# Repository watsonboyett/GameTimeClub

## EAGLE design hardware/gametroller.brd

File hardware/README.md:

## Revision History

### Rev. A

* Initial design

### Rev. B

* Added "power good" LED to 3V3 rail
* Removed silkscreen text for part numbers (just not enough room)
* Increased voltage output on 5V step-down converter 
* Added silkscreen text for pin numbers
* Fixed USB A pins (data lines were backwards)
* Added vias to micro USB shield pads to provide better mechanical support
* Added PTC fuse to micro USB port for over-current protection

### Future Changes

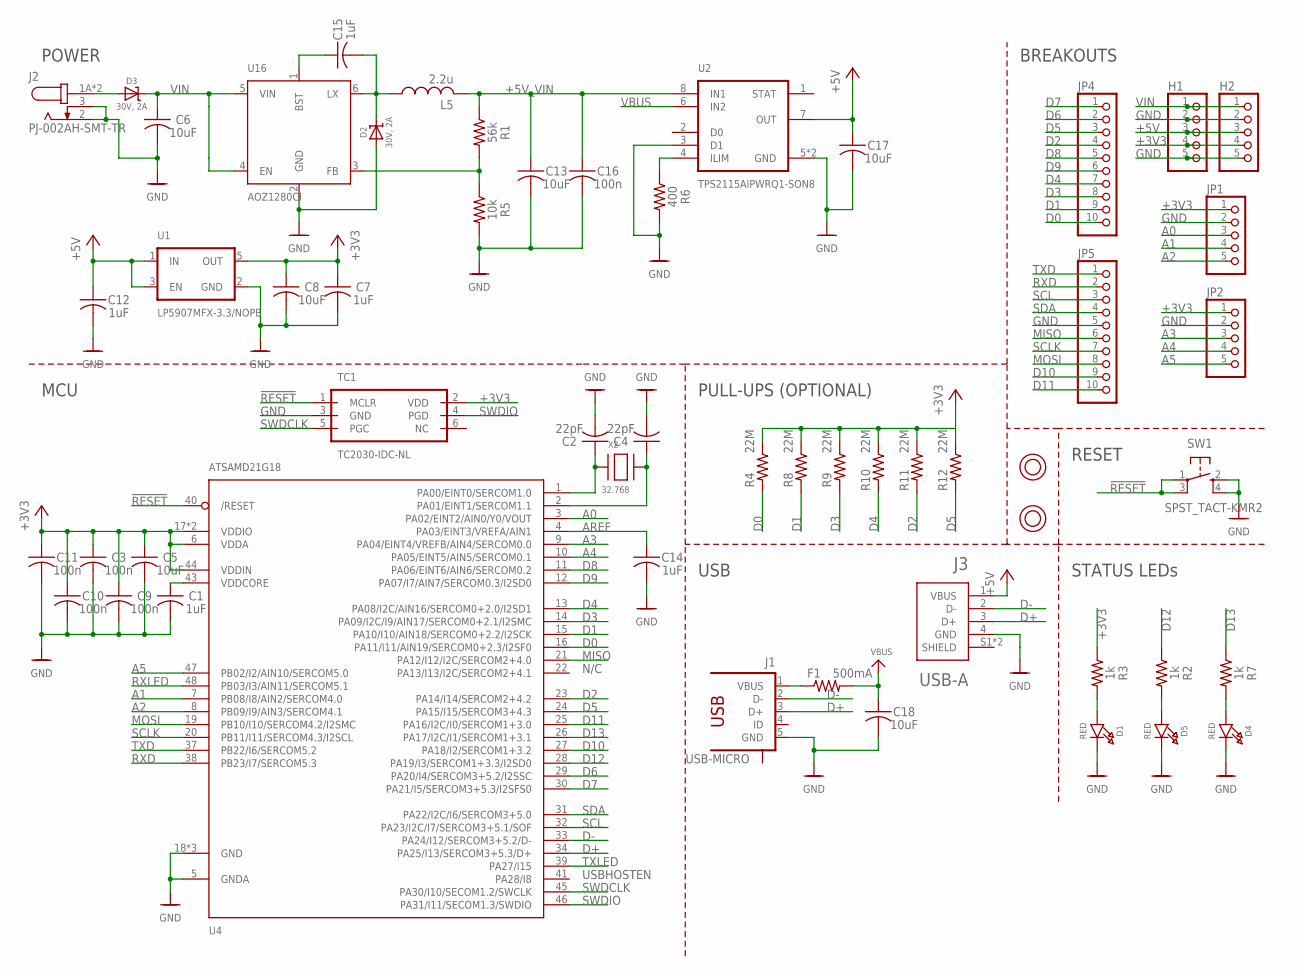
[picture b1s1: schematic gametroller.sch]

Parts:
C1, C7, C12, C14, C15: 1uF; C0603; MPN 0603ZC105KAT2A
C2, C4: 22pF; C0603; MPN C0603C220K4GACTU
C3, C9, C10, C11, C16: 100n; C0603; MPN C0603X104K5RAC7867
C5, C6, C8, C13, C17, C18: 10uF; C0805; MPN C2012JB1E106K085AC
D1, D4, D5: RED; CHIPLED_0805_NOOUTLINE; MPN LTST-C170GKT
D2, D3: 30V, 2A; SOD-128; MPN CMS06(TE12L,Q,M)
F1: 500mA; R0603; MPN MF-FSMF050X-2
H1, H2: PINHD-1X5-SMT; 1X05-SMT
J1: USB-MICRO; USB-10118192-0001LF
J2: PJ-002AH-SMT-TR; CUI_PJ-002AH-SMT-TR
J3: USB-A; CUI_UJ2-AH-1-SMT
JP1, JP2: PINHD-1X5-SMT; 1X05-SMT
JP4, JP5: PINHD-1X10-SMT; 1X10-SMT
L5: 2.2u; L5050M; MPN TYS50402R2N-10
R1: 56k; R0603; MPN ERJ-3EKF5602V
R2, R3, R7: 1k; R0603; MPN ERJ-3EKF1001V
R4, R8, R9, R10, R11, R12: 22M; R0603; MPN ERJ-3GEYK226V
R5: 10k; R0603; MPN ERJ-3GEYJ103V
R6: 400; R0603; MPN ERJ-3EKF4020V
SW1: SPST_TACT-KMR2; KMR2; MPN KMR211GLFS
TC1: TC2030-IDC-NL
U1: LP5907MFX-3.3/NOPB; SOT95P280X145-5N
U2: TPS2115AIPWRQ1-SON8; SON65P300X300X100-9N
U4: ATSAMD21G18; TQFP48_7MM
U16: AOZ1280CI; SOT-23-6
U$7, U$9: TERM-7774
X2: 32.768; XTAL3215; MPN ECS-.327-12.5-34B-TR

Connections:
!RESET: SW1.1, SW1.3 (P1), TC1.1 (MCLR), U4.40 (/RESET)
+3V3: C3.1, C5.1, C7.1, C8.1, C9.1, C10.1, C11.1, H1.4, H2.4, JP1.1, JP2.1, R3.1, R4.1, R8.1, R9.1, R10.1, R11.1, R12.1, TC1.2 (VDD), U1.5 (OUT), U4.6 (VDDA), U4.17 (VDDIO), U4.36 (VDDIO), U4.44 (VDDIN)
+5V: C12.1, C17.1, H1.3, H2.3, J3.1 (VBUS), U1.1 (IN), U1.3 (EN), U2.7 (OUT)
+5V_VIN: C13.1, C16.1, L5.2, R1.1, U2.8 (IN1)
A0: JP1.3, U4.3 (PA02/EINT2/AIN0/Y0/VOUT)
A1: JP1.4, U4.7 (PB08/I8/AIN2/SERCOM4.0)
A2: JP1.5, U4.8 (PB09/I9/AIN3/SERCOM4.1)
A3: JP2.3, U4.9 (PA04/EINT4/VREFB/AIN4/SERCOM0.0)
A4: JP2.4, U4.10 (PA05/EINT5/AIN5/SERCOM0.1)
A5: JP2.5, U4.47 (PB02/I2/AIN10/SERCOM5.0)
AREF: C14.1, U4.4 (PA03/EINT3/VREFA/AIN1)
D0: JP4.10, R4.2, U4.16 (PA11/I11/AIN19/SERCOM0+2.3/I2SF0)
D1: JP4.9, R8.2, U4.15 (PA10/I10/AIN18/SERCOM0+2.2/I2SCK)
D2: JP4.4, R11.2, U4.23 (PA14/I14/SERCOM2+4.2)
D3: JP4.8, R9.2, U4.14 (PA09/I2C/I9/AIN17/SERCOM0+2.1/I2SMC)
D4: JP4.7, R10.2, U4.13 (PA08/I2C/AIN16/SERCOM0+2.0/I2SD1)
D5: JP4.3, R12.2, U4.24 (PA15/I15/SERCOM3+4.3)
D6: JP4.2, U4.29 (PA20/I4/SERCOM3+5.2/I2SSC)
D7: JP4.1, U4.30 (PA21/I5/SERCOM3+5.3/I2SFS0)
D8: JP4.5, U4.11 (PA06/EINT6/AIN6/SERCOM0.2)
D9: JP4.6, U4.12 (PA07/I7/AIN7/SERCOM0.3/I2SD0)
D10: JP5.9, U4.27 (PA18/I2/SERCOM1+3.2)
D11: JP5.10, U4.25 (PA16/I2C/I0/SERCOM1+3.0)
D12: R2.1, U4.28 (PA19/I3/SERCOM1+3.3/I2SD0)
D13: R7.1, U4.26 (PA17/I2C/I1/SERCOM1+3.1)
D+: J1.3 (D+), J3.3 (D+), U4.34 (PA25/I13/SERCOM3+5.3/D+)
D-: J1.2 (D-), J3.2 (D-), U4.33 (PA24/I12/SERCOM3+5.2/D-)
GND: C1.2, C2.2, C3.2, C4.2, C5.2, C6.2, C7.2, C8.2, C9.2, C10.2, C11.2, C12.2, C13.2, C14.2, C16.2, C17.2, C18.2, D1.C, D2.A, D4.C, D5.C, H1.2, H1.5, H2.2, H2.5, J1.5 (GND), J2.2, J2.3, J3.4 (GND), JP1.2, JP2.2, JP5.5, R5.2, R6.2, SW1.2 (S), SW1.4 (S1), TC1.3 (GND), U1.2 (GND), U2.3 (D1), U2.5 (GND), U2.9 (GND), U4.5 (GNDA), U4.18 (GND), U4.35 (GND), U4.42 (GND), U16.2 (GND)
LX: C15.2, D2.C, L5.1, U16.6 (LX)
MISO: JP5.6, U4.21 (PA12/I12/I2C/SERCOM2+4.0)
MOSI: JP5.8, U4.19 (PB10/I10/SERCOM4.2/I2SMC)
unnamed: D5.A, R2.2
unnamed: D4.A, R7.2
unnamed: D1.A, R3.2
unnamed: F1.1, J1.1 (VBUS)
unnamed: C2.1, U4.1 (PA00/EINT0/SERCOM1.0), X2.P$1
unnamed: C4.1, U4.2 (PA01/EINT1/SERCOM1.1), X2.P$2
unnamed: C15.1, U16.1 (BST)
unnamed: R6.1, U2.4 (ILIM)
unnamed: R1.2, R5.1, U16.3 (FB)
RXD: JP5.2, U4.38 (PB23/I7/SERCOM5.3)
RXLED: U4.48 (PB03/I3/AIN11/SERCOM5.1)
SCL: JP5.3, U4.32 (PA23/I2C/I7/SERCOM3+5.1/SOF)
SCLK: JP5.7, U4.20 (PB11/I11/SERCOM4.3/I2SCL)
SDA: JP5.4, U4.31 (PA22/I2C/I6/SERCOM3+5.0)
SWDCLK: TC1.5 (PGC), U4.45 (PA30/I10/SECOM1.2/SWCLK)
SWDIO: TC1.4 (PGD), U4.46 (PA31/I11/SECOM1.3/SWDIO)
TXD: JP5.1, U4.37 (PB22/I6/SERCOM5.2)
TXLED: U4.39 (PA27/I15)
VBUS: C18.1, F1.2, U2.6 (IN2)
VDDCORE: C1.1, U4.43 (VDDCORE)
VIN: C6.1, D3.C, H1.1, H2.1, U16.4 (EN), U16.5 (VIN)
VIN_PRE: D3.A, J2.1A (1), J2.1B (1)

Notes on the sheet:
POWER
RESET
N/C
USBHOSTEN
BREAKOUTS
STATUS LEDs
MCU
USB
PULL-UPS (OPTIONAL)

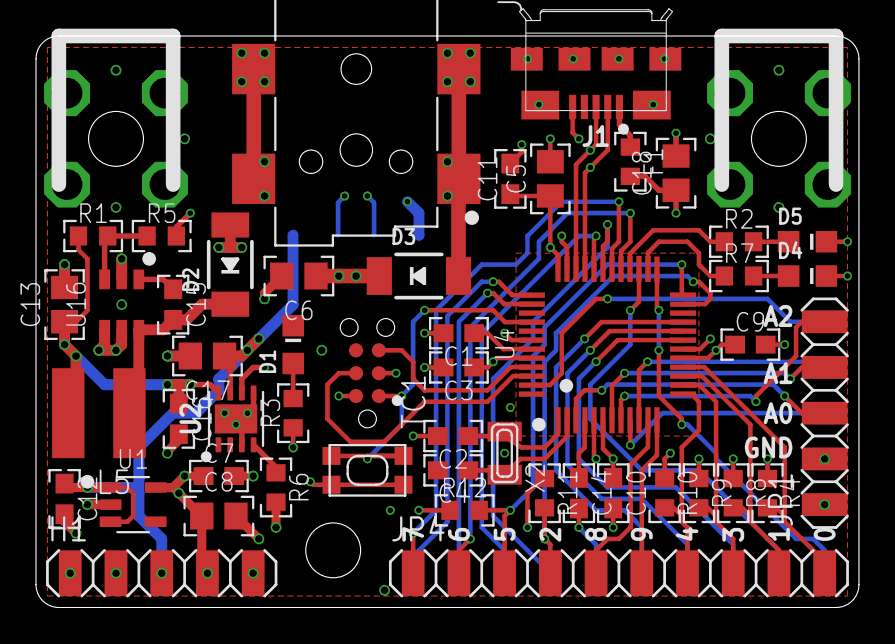
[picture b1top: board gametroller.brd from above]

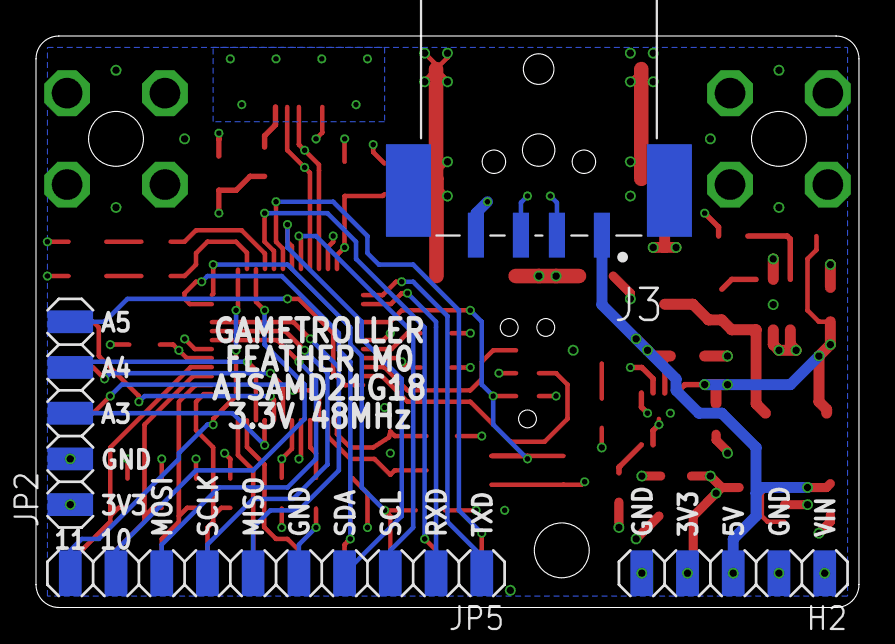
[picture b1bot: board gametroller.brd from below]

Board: 4 copper layers, 45.7 x 31.8 mm, 58 parts (4 on the bottom side), 51 nets.

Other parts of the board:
U$12, U$13, U$15: HOLE_4-40

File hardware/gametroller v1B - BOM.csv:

"Qty";"Value";"Device";"Package";"Parts";"Description";"MFG";"MPN";"PN-DK";
"2";"";"PINHD-1X10-SMT";"1X10-SMT";"JP4, JP5";"PIN HEADER";"";"";"";
"4";"";"PINHD-1X5-SMT";"1X05-SMT";"H1, H2, JP1, JP2";"PIN HEADER";"";"";"";
"5";"100n";"C-USC0603";"C0603";"C3, C9, C10, C11, C16";"CAPACITOR, American symbol";"KEMET";"C0603X104K5RAC7867";"399-7969-1-ND";
"1";"10k";"R-US_R0603";"R0603";"R5";"RESISTOR, American symbol";"Panasonic Electronic Components";"ERJ-3GEYJ103V";"P10KGCT-ND";
"6";"10uF";"C-USC0805";"C0805";"C5, C6, C8, C13, C17, C18";"CAPACITOR, American symbol";"TDK Corporation";"C2012JB1E106K085AC";"445-11462-1-ND";
"3";"1k";"R-US_R0603";"R0603";"R2, R3, R7";"RESISTOR, American symbol";"Panasonic Electronic Components";"ERJ-3EKF1001V";"P1.00KHCT-ND";
"5";"1uF";"C-USC0603";"C0603";"C1, C7, C12, C14, C15";"CAPACITOR, American symbol";"AVX Corporation";"0603ZC105KAT2A";"478-7940-1-ND";
"1";"2.2u";"L-USL5050M";"L5050M";"L5";"INDUCTOR, American symbol";"Laird-Signal Integrity Products";"TYS50402R2N-10";"240-2714-1-ND";
"6";"22M";"R-US_R0603";"R0603";"R4, R8, R9, R10, R11, R12";"RESISTOR, American symbol";"Panasonic Electronic Components";"ERJ-3GEYK226V";"P22MGCT-ND";
"2";"22pF";"C-USC0603";"C0603";"C2, C4";"CAPACITOR, American symbol";"KEMET";"C0603C220K4GACTU";"399-9031-1-ND";
"2";"30V, 2A";"DIODE-SCHOTTKYSOD-128";"SOD-128";"D2, D3";"";"Toshiba Semiconductor and Storage";"CMS06(TE12L,Q,M)";"CMS06QMCT-ND";
"1";"32.768";"XTAL-3.2X1.5";"XTAL3215";"X2";"Low cost SMT crystals, no capacitors included";"ECS Inc.";"ECS-.327-12.5-34B-TR";"XC1617CT-ND";
"1";"400";"R-US_R0603";"R0603";"R6";"RESISTOR, American symbol";"Panasonic Electronic Components";"ERJ-2RKF4020X";"P402LCT-ND";
"1";"500mA";"R-US_R0603";"R0603";"F1";"RESISTOR, American symbol";"Bel Fuse Inc.";"0ZCK0050FF2E";"507-1813-1-ND";
"1";"56k";"R-US_R0603";"R0603";"R1";"RESISTOR, American symbol";"Panasonic Electronic Components";"ERJ-3EKF5602V";"P56.0KHCT-ND";
"1";"AOZ1280CI";"AOZ1280CI";"SOT-23-6";"U16";"IC REG BUCK ADJ 1.2A SOT23-6";"Alpha & Omega Semiconductor Inc.";"AOZ1280CI";"785-1277-1-ND";
"1";"ATSAMD21G18";"ATSAMD21J_QFP";"TQFP48_7MM";"U4";"ARM® Cortex®-M0+ SAM D21G Microcontroller IC 32-Bit 48MHz 256KB (256K x 8) FLASH";"Microchip Technology";"ATSAMD21G18A";"ATSAMD21G18A-AU-ND";
"1";"LP5907MFX-3.3/NOPB";"LP5907MFX-3.3/NOPB";"SOT95P280X145-5N";"U1";"IC REG LINEAR 3.3V 250MA SOT23";"Texas Instruments";"LP5907MFX-3.3/NOPB";"296-38557-1-ND";
"1";"PJ-002AH-SMT-TR";"PJ-002AH-SMT-TR";"CUI_PJ-002AH-SMT-TR";"J2";"Power Barrel Connector Jack 2.00mm ID (0.079"), 5.50mm OD (0.217")";"CUI";"PJ-002AH-SMT-TR";"CP-002AHPJCT-ND";
"3";"RED";"LED0805_NOOUTLINE";"CHIPLED_0805_NOOUTLINE";"D1, D4, D5";"LED";"Lite-On Inc.";"LTST-C170GKT";"160-1179-1-ND";
"1";"SPST_TACT-KMR2";"SPST_TACT-KMR2";"KMR2";"SW1";"SMT 6mm switch, EVQQ2 series";"C&K";"KMR211GLFS";"401-1426-1-ND";
"1";"TC2030-IDC-NL";"TC2030-IDC-NL";"TC2030-IDC-NL";"TC1";"Tag-Connect In Circuit Programming & Debug Cable 6 Pin";"Tag-Connect";"TC2030-IDC";"";
"2";"TERM-7774";"TERM-7774";"TERM-7774";"U$7, U$9";"TERM SCREW 4-40 4 PIN PCB RA";"Keystone Electronics";"7774";"36-7774-ND";
"1";"TPS2115AIPWRQ1-SON8";"TPS2115AIPWRQ1-SON8";"SON65P300X300X100-9N";"U2";"AUTO-SWITCHING POWER MULTIPLEXER";"Texas Instruments";"TPS2115ADRBR";"296-23394-1-ND";
"1";"USB-A";"USB-A";"CUI_UJ2-AH-1-SMT";"J3";"USB - A USB 2.0 Receptacle Connector";"CUI";"UJ2-AH-1-SMT-TR";"102-4133-1-ND";
"1";"USB-MICRO";"USB-MICRO";"USB-10118192-0001LF";"J1";"CONN USB MICRO B RECPT SMT R/A";"Amphenol";"10118192-0001LF";"609-4613-1-ND";

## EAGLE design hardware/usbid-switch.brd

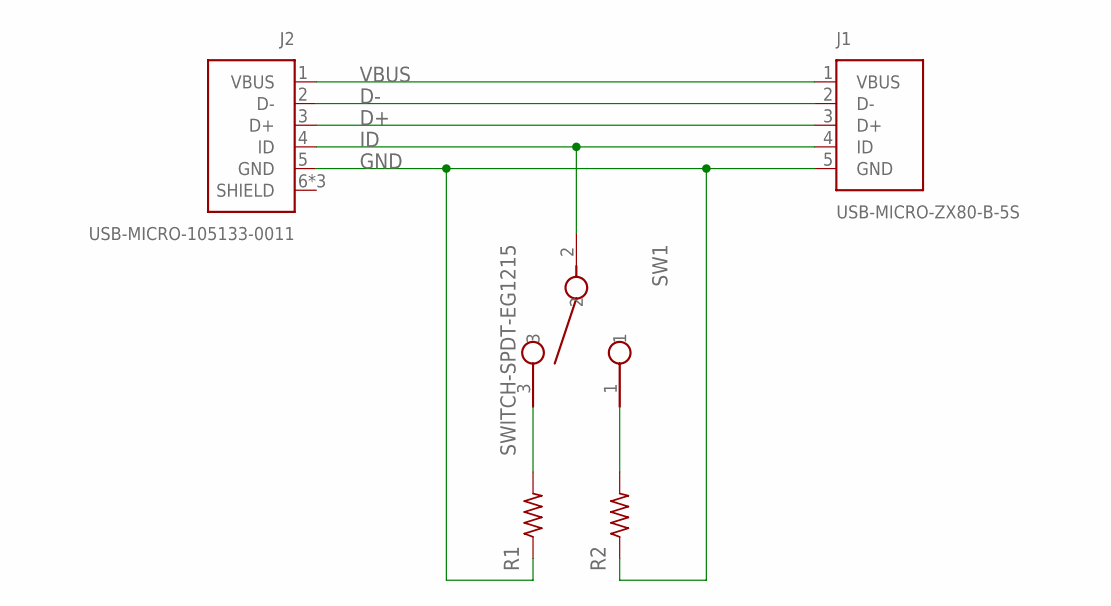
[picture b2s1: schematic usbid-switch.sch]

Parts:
J1: USB-MICRO-ZX80-B-5S; HRS_ZX80-B-5S
J2: USB-MICRO-105133-0011; MOLEX_105133-0011
R1, R2: R-US_R0603; R0603
SW1: SWITCH-SPDT-EG1215; EG1215

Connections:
D+: J1.3 (D+), J2.3 (D+)
D-: J1.2 (D-), J2.2 (D-)
GND: J1.5 (GND), J2.5 (GND), R1.1, R2.1
ID: J1.4 (ID), J2.4 (ID), SW1.2
unnamed: R1.2, SW1.3
unnamed: R2.2, SW1.1
VBUS: J1.1 (VBUS), J2.1 (VBUS)

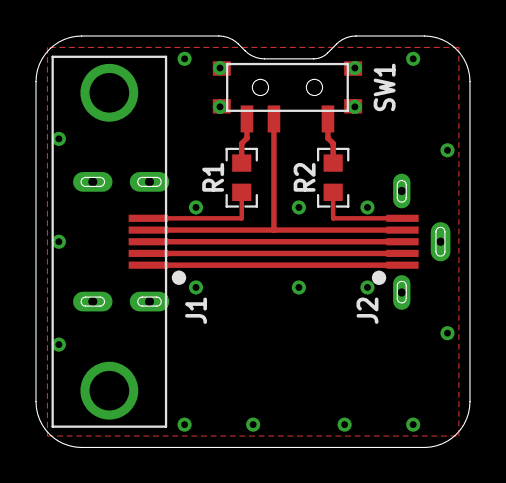
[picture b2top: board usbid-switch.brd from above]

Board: 2 copper layers, 24.1 x 22.9 mm, 5 parts (0 on the bottom side), 7 nets.

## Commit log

2018-08-25 Minor changes to PCB
    * Added "power good" LED to 3V3 rail
    * Removed silkscreen text for part numbers (just not enough room)
    * Increased voltage output on 5V step-down converter
    * Added silkscreen text for pin numbers
2018-08-25 Added support for start/select buttons and removed Serial console print statements
2018-08-25 Renamed repo and moved files around
2018-09-22 Added USB-ID selector switch design files
2018-09-29 Minor modifications and cleanup to PCB
2018-09-30 Added 22M pullup resistors to several IO pins to allow board to be used as a MaKeyMaKey clone
2018-09-30 Added initial clone/mod of MaKeyMaKey firmware
2018-10-04 Updated BOM attributes for currently available parts
2018-10-05 Fixed some DFM and CAM output issues.
2019-01-11 Minor hardware tweaks
2019-01-11 Changed MaKey clone pins to map to keyboard keys rather than mouse movements

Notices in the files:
Gametroller/hardware/gametroller.sch:
CONTACT_PHONE: Licensed under CC-BY-SA
